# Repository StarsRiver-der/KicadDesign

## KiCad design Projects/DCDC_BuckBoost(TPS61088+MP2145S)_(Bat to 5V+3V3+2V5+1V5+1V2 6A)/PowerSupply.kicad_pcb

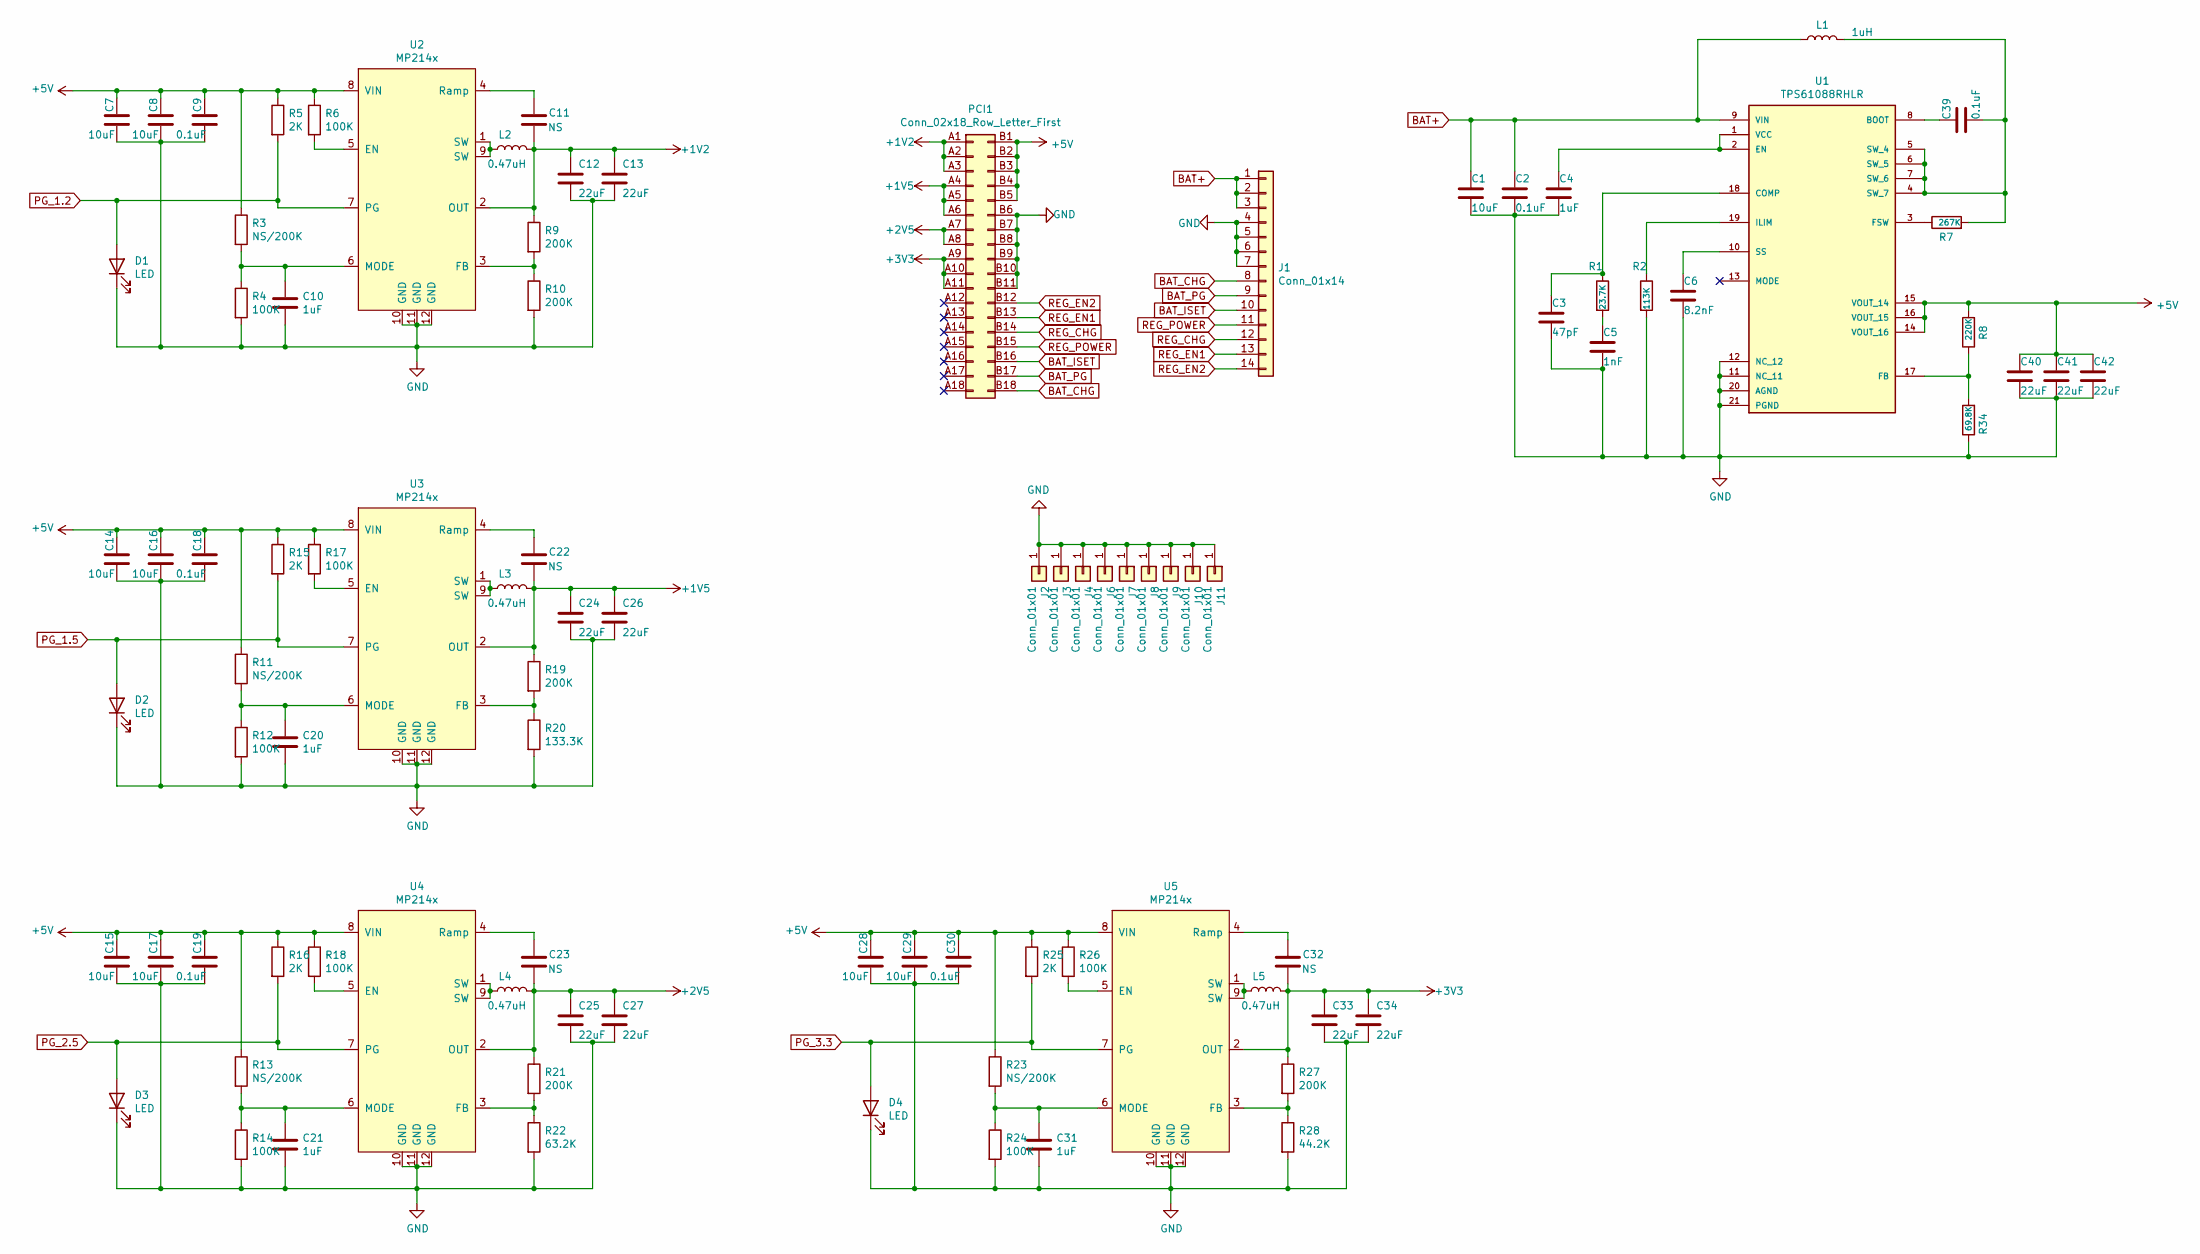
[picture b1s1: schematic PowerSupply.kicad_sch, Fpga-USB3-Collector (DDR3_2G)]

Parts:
C1, C7, C8, C14, C15, C16, C17, C28, C29: 10uF; C_0603_1608Metric
C2, C9, C18, C19, C30, C39: 0.1uF; C_0402_1005Metric
C3: 47pF; C_0402_1005Metric
C4, C10, C20, C21, C31: 1uF; C_0402_1005Metric
C5: 1nF; C_0402_1005Metric
C6: 8.2nF; C_0402_1005Metric
C11, C22, C23, C32: NS; C_0402_1005Metric
C12, C13, C24, C25, C26, C27, C33, C34, C40, C41, C42: 22uF; C_0603_1608Metric
D1, D2, D3, D4: LED; LED_0402_1005Metric
J1: Conn_01x14; Hirose_FH12-14S-0.5SH_1x14-1MP_P0.50mm_Horizontal
J2, J3, J4, J6, J7, J8, J9, J10, J11: Conn_01x01; pad-6-1.5
L1: 1uH; L_Sunlord_MWSA0518_5.4x5.2mm
L2, L3, L4, L5: 0.47uH; L_Sunlord_MWSA0518_5.4x5.2mm
PCI1: Conn_02x18_Row_Letter_First; BUS_PCIexpress_x1
R1: 23.7K; R_0402_1005Metric
R2: 113K; R_0402_1005Metric
R3, R11, R13, R23: NS/200K; R_0402_1005Metric
R4, R6, R12, R14, R17, R18, R24, R26: 100K; R_0402_1005Metric
R5, R15, R16, R25: 2K; R_0402_1005Metric
R7: 267K; R_0402_1005Metric
R8: 220K; R_0402_1005Metric
R9, R10, R19, R21, R27: 200K; R_0402_1005Metric
R20: 133.3K; R_0402_1005Metric
R22: 63.2K; R_0402_1005Metric
R28: 44.2K; R_0402_1005Metric
R34: 69.8K; R_0402_1005Metric
U1: TPS61088RHLR; IC_TPS61088RHLR; PARTREV 4219071/A 05/2017
U2, U3, U4, U5: MP214x; MP2145_2147_DG_Z

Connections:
+1V2: C11.1, C12.1, C13.1, L2.2, PCI1.A1, PCI1.A2, PCI1.A3, R9.1, U2.2 (OUT)
+1V5: C22.1, C24.1, C26.1, L3.2, PCI1.A4, PCI1.A5, PCI1.A6, R19.1, U3.2 (OUT)
+2V5: C23.1, C25.1, C27.1, L4.2, PCI1.A7, PCI1.A8, R21.1, U4.2 (OUT)
+3V3: C32.1, C33.1, C34.1, L5.2, PCI1.A9, PCI1.A10, PCI1.A11, R27.1, U5.2 (OUT)
+5V: C7.1, C8.1, C9.1, C14.1, C15.1, C16.1, C17.1, C18.1, C19.1, C28.1, C29.1, C30.1, C40.1, C41.1, C42.1, PCI1.B1, PCI1.B2, PCI1.B3, PCI1.B4, PCI1.B5, R3.1, R5.1, R6.1, R8.2, R11.1, R13.1, R15.1, R16.1, R17.1, R18.1, R23.1, R25.1, R26.1, U1.14 (VOUT_16), U1.15 (VOUT_14), U1.16 (VOUT_15), U2.8 (VIN), U3.8 (VIN), U4.8 (VIN), U5.8 (VIN)
BAT+: C1.1, C2.1, J1.1, J1.2, J1.3, L1.1, U1.9 (VIN)
BAT_CHG: J1.8, PCI1.B18
BAT_ISET: J1.10, PCI1.B16
BAT_PG: J1.9, PCI1.B17
GND: C1.2, C2.2, C3.2, C4.2, C5.2, C6.2, C7.2, C8.2, C9.2, C10.2, C12.2, C13.2, C14.2, C15.2, C16.2, C17.2, C18.2, C19.2, C20.2, C21.2, C24.2, C25.2, C26.2, C27.2, C28.2, C29.2, C30.2, C31.2, C33.2, C34.2, C40.2, C41.2, C42.2, D1.1 (K), D2.1 (K), D3.1 (K), D4.1 (K), J1.4, J1.5, J1.6, J1.7, J2.1, J3.1, J4.1, J6.1, J7.1, J8.1, J9.1, J10.1, J11.1, PCI1.B6, PCI1.B7, PCI1.B8, PCI1.B9, PCI1.B10, PCI1.B11, R2.2, R4.2, R10.2, R12.2, R14.2, R20.2, R22.2, R24.2, R28.2, R34.1, U1.11 (NC_11), U1.12 (NC_12), U1.20 (AGND), U1.21 (PGND), U2.10 (GND), U2.11 (GND), U2.12 (GND), U3.10 (GND), U3.11 (GND), U3.12 (GND), U4.10 (GND), U4.11 (GND), U4.12 (GND), U5.10 (GND), U5.11 (GND), U5.12 (GND)
unnamed: C3.1, R1.1, U1.18 (COMP)
unnamed: C4.1, U1.1 (VCC), U1.2 (EN)
unnamed: C5.1, R1.2
unnamed: C6.1, U1.10 (SS)
unnamed: C10.1, R3.2, R4.1, U2.6 (MODE)
unnamed: C11.2, U2.4 (Ramp)
unnamed: C20.1, R11.2, R12.1, U3.6 (MODE)
unnamed: C21.1, R13.2, R14.1, U4.6 (MODE)
unnamed: C22.2, U3.4 (Ramp)
unnamed: C23.2, U4.4 (Ramp)
unnamed: C31.1, R23.2, R24.1, U5.6 (MODE)
unnamed: C32.2, U5.4 (Ramp)
unnamed: C39.1, U1.8 (BOOT)
unnamed: C39.2, L1.2, R7.2, U1.4 (SW_7), U1.5 (SW_4), U1.6 (SW_5), U1.7 (SW_6)
unnamed: L2.1, U2.1 (SW), U2.9 (SW)
unnamed: L3.1, U3.1 (SW), U3.9 (SW)
unnamed: L4.1, U4.1 (SW), U4.9 (SW)
unnamed: L5.1, U5.1 (SW), U5.9 (SW)
unnamed: R2.1, U1.19 (ILIM)
unnamed: R6.2, U2.5 (EN)
unnamed: R7.1, U1.3 (FSW)
unnamed: R9.2, R10.1, U2.3 (FB)
unnamed: R17.2, U3.5 (EN)
unnamed: R18.2, U4.5 (EN)
unnamed: R19.2, R20.1, U3.3 (FB)
unnamed: R21.2, R22.1, U4.3 (FB)
unnamed: R26.2, U5.5 (EN)
unnamed: R27.2, R28.1, U5.3 (FB)
unnamed: R8.1, R34.2, U1.17 (FB)
PG_1.2: D1.2 (A), R5.2, U2.7 (PG)
PG_1.5: D2.2 (A), R15.2, U3.7 (PG)
PG_2.5: D3.2 (A), R16.2, U4.7 (PG)
PG_3.3: D4.2 (A), R25.2, U5.7 (PG)
REG_CHG: J1.12, PCI1.B14
REG_EN1: J1.13, PCI1.B13
REG_EN2: J1.14, PCI1.B12
REG_POWER: J1.11, PCI1.B15

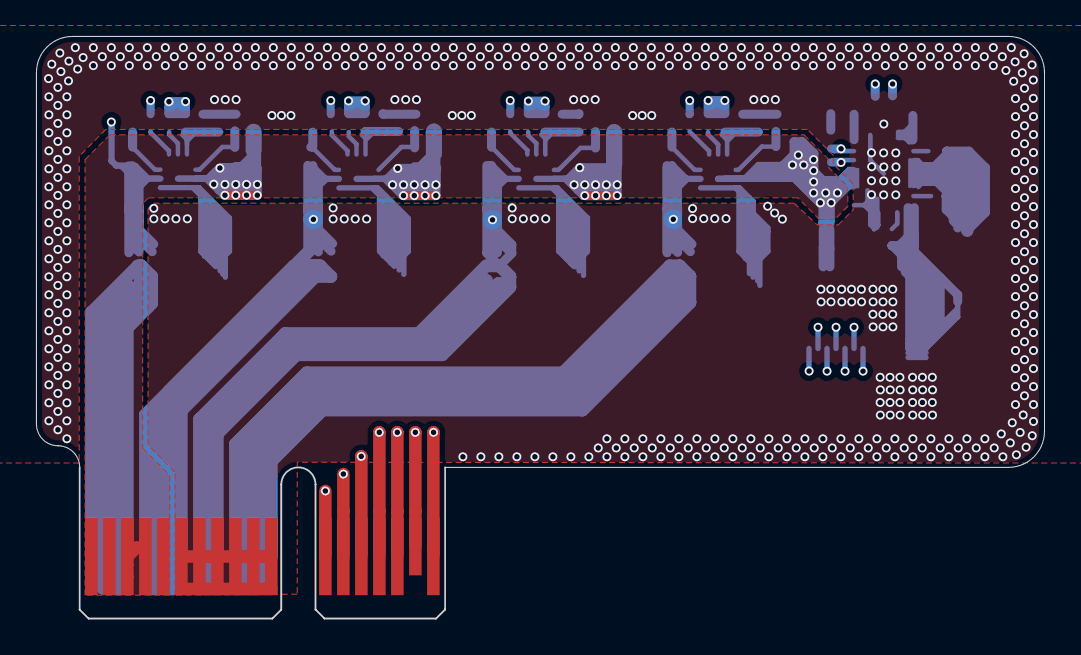
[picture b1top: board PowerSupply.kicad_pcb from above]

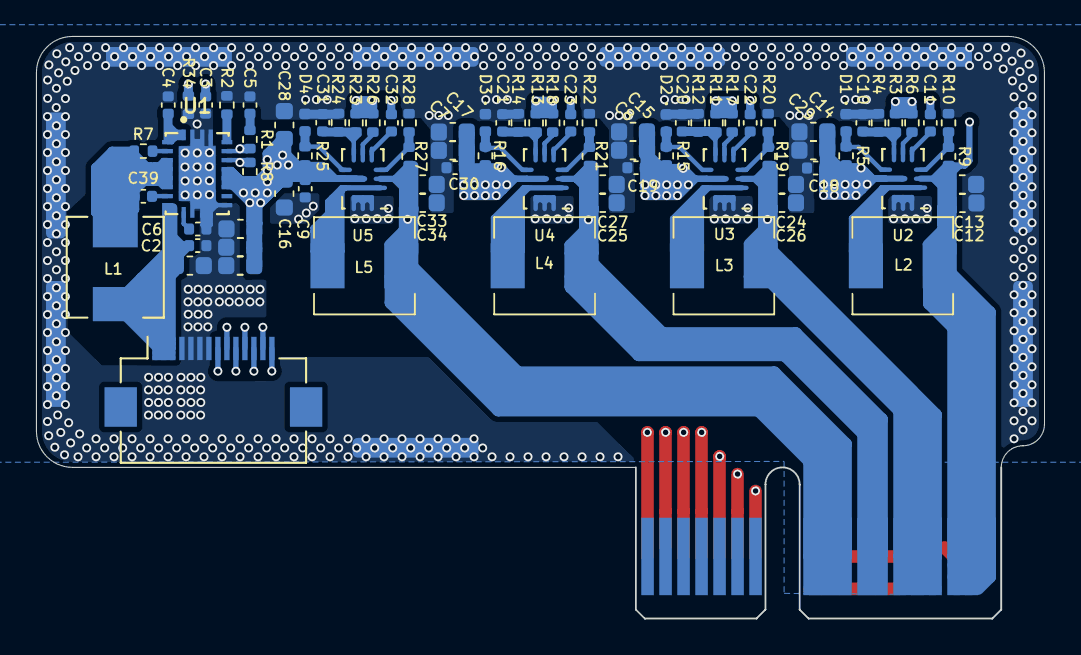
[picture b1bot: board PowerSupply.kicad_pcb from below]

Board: 4 copper layers, 56.0 x 32.3 mm, 92 parts (91 on the bottom side), 47 nets.

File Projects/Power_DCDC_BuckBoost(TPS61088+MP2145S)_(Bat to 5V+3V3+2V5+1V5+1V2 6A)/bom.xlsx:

标号 | 数量/板 | 值 | 备注 | 封装 | 数量 | 单价 | 总价
C1, C7, C8, C14, C15, C16, C17, C28, C29 | 9 | 10uF |  | 0603 | 100 | 0 | 0
C2, C9, C18, C19, C30, C39 | 6 | 0.1uF |  | 0402 | 100 | 0 | 0
C3 | 1 | 47pF |  | 0402 | 100 | 0 | 0
C4, C10, C20, C21, C31 | 5 | 1uF |  | 0402 | 100 | 0 | 0
C5 | 1 | 1nF |  | 0402 | 100 | 0 | 0
C6 | 1 | 8.2nF |  | 0402 | 100 | 0 | 0
C11, C22, C23, C32 | 4 | NS |  | 0402 | 100 | 0 | 0
C12, C13, C24, C25, C26, C27, C33, C34, C40, C41, C42 | 11 | 22uF |  | 0603 | 100 | 0 | 0
D1, D2, D3, D4 | 4 | LED |  | 0402 | 100 | 0 | 0
J1 | 1 | Conn_01x14 |  | FPC:14S-0.5SH | 100 | 0 | 0
L1 | 1 | 1uH |  | 0530 | 100 | 0 | 0
L2, L3, L4, L5 | 4 | 0.47uH |  | 0530 | 100 | 0 | 0
R1 | 1 | 23.7K |  | 0402 | 100 | 0 | 0
R2 | 1 | 113K |  | 0402 | 100 | 0 | 0
R3, R11, R13, R23 | 4 | NS/200K |  | 0402 | 100 | 0 | 0
R4, R6, R12, R14, R17, R18, R24, R26 | 8 | 100K |  | 0402 | 100 | 0 | 0
R5, R15, R16, R25 | 4 | 2K |  | 0402 | 100 | 0 | 0
R7 | 1 | 267K |  | 0402 | 100 | 0 | 0
R8 | 1 | 220K |  | 0402 | 100 | 0 | 0
R9, R10, R19, R21, R27 | 5 | 200K |  | 0402 | 100 | 0 | 0
R20 | 1 | 133.3K |  | 0402 | 100 | 0 | 0
R22 | 1 | 63.2K |  | 0402 | 100 | 0 | 0
R28 | 1 | 44.2K |  | 0402 | 100 | 0 | 0
R34 | 1 | 69.8K |  | 0402 | 100 | 0 | 0
U1 | 1 | TPS61088RHLR |  | TPS61088RHLR | 100 | 0 | 0
U2, U3, U4, U5 | 4 | MP2145 |  | MP2145 | 100 | 0 | 0

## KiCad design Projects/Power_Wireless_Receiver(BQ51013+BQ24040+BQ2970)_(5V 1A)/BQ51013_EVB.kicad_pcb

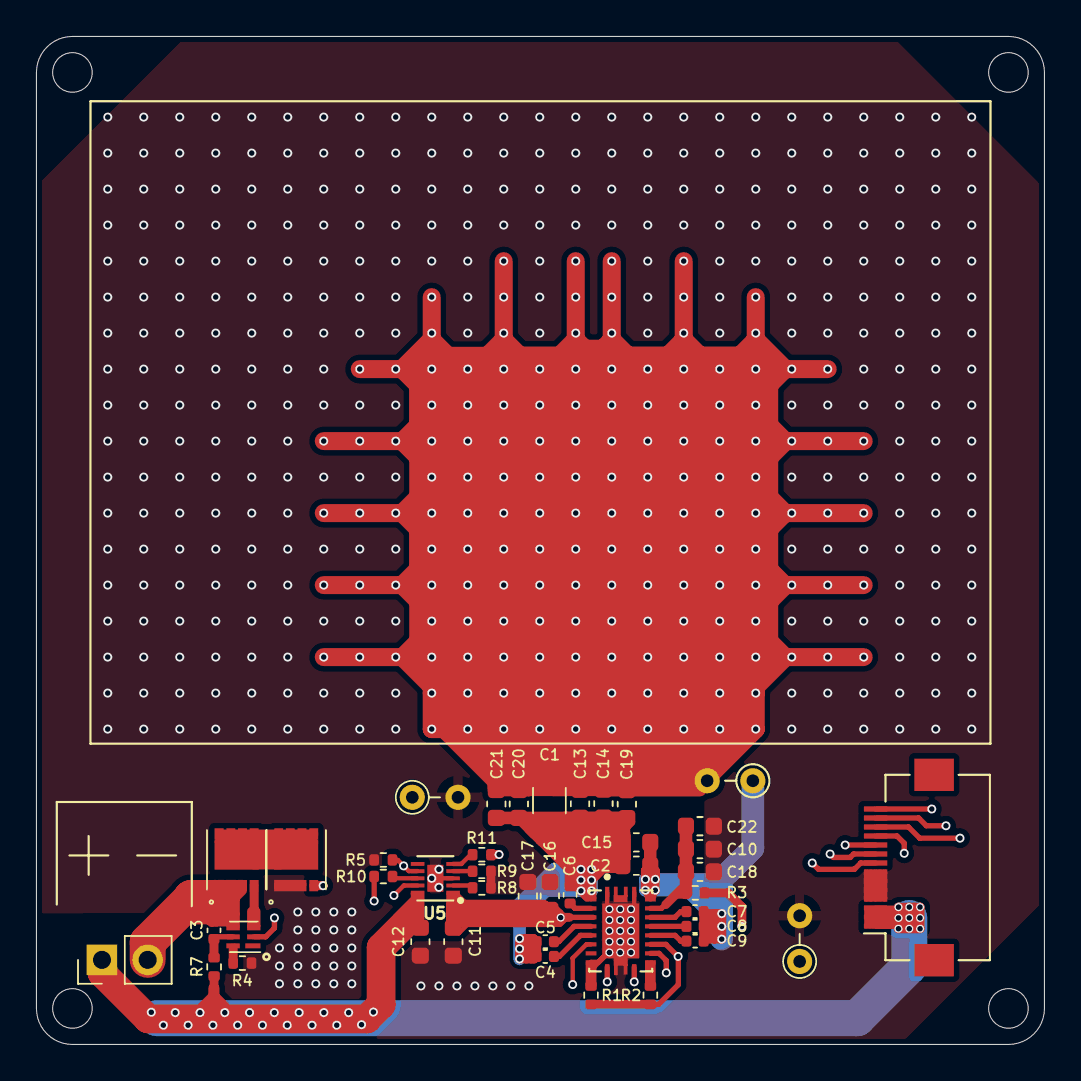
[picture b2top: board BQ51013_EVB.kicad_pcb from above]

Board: 4 copper layers, 56.0 x 56.0 mm, 46 parts (0 on the bottom side), 33 nets.

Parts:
C1: 100nF; C_1206_3216Metric
C2, C15: 1nF; C_0603_1608Metric
C3: 100nF; C_0402_1005Metric
C4, C9: 22nF; C_0402_1005Metric
C5, C8: 470nF; C_0402_1005Metric
C6, C7: 10nF; C_0402_1005Metric
C10, C16, C22: 10uF; C_0603_1608Metric
C11, C12: 1uF; C_0603_1608Metric
C13, C14, C19, C20: 10nF; C_0603_1608Metric
C17, C18: 0.1uF; C_0603_1608Metric
C21: 2.2nF; C_0603_1608Metric
J1, J2, J3, J4: Conn_01x01_Female; MountingHole_2.2mm_M2
J5: BAT; PinHeader_1x02_P2.54mm_Vertical
J6: AC; R_Axial_DIN0204_L3.6mm_D1.6mm_P2.54mm_Vertical
J7: Conn_01x14; Hirose_FH12-14S-0.5SH_1x14-1MP_P0.50mm_Horizontal
R1: 196R; R_0402_1005Metric
R2: 20R; R_0402_1005Metric
R3: 20k; R_0402_1005Metric
R4: 2.2k; R_0402_1005Metric
R5: 1k; R_0402_1005Metric
R7: 330R; R_0402_1005Metric
R8: 536R; R_0402_1005Metric
R9: 2K; R_0402_1005Metric
R10, R11: 1.5K; R_0402_1005Metric
TH1, TH2: Thermistor_NTC; R_Axial_DIN0204_L3.6mm_D1.6mm_P2.54mm_Vertical
U1: BQ2971; WSON-6_1.5x1.5mm_P0.5mm
U2: BQ51013BRHLR
U3, U4: CSD16406Q3
U5: BQ24040DSQT

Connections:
BAT+: C12.1, J5.1, J7.1, J7.2, J7.3, R7.1, U5.10 (OUT)
BAT-: C3.2, J5.2, U1.4 (VSS), U4.1, U4.2, U4.3
BAT_CHG: J7.8, R10.2
BAT_ISET: J7.10, R5.1, U5.7 (ISET2)
BAT_PG: J7.9, R11.2
GND: C10.1, C11.1, C12.2, C16.1, C17.1, C18.1, C22.1, J7.4, J7.5, J7.6, J7.7, R1.2, R4.2, R5.2, R8.2, R9.2, TH1.2, TH2.2, U2.1 (PGND), U2.9 (AD), U2.20 (PGND), U2.21 (EXP), U3.1, U3.2, U3.3, U5.3 (VSS), U5.11 (EP)
unnamed: C1.1, C13.1, C14.1, C19.1, C20.1, C21.1, J6.2
unnamed: C1.2, C2.1, C4.1, C5.1, C6.1, C13.2, C14.2, C15.1, C19.2, C20.2, C21.2, U2.2 (AC1)
unnamed: C3.1, R7.2, U1.5 (BAT)
unnamed: C4.2, U2.6 (COMM1)
unnamed: C5.2, U2.5 (CLAMP1)
unnamed: C6.2, U2.3 (BOOT1)
unnamed: C7.1, U2.17 (BOOT2)
unnamed: C8.1, U2.16 (CLAMP2)
unnamed: C9.1, U2.15 (COMM2)
unnamed: C10.2, C18.2, C22.2, R3.1, U2.18 (RECT)
unnamed: C2.2, C7.2, C8.2, C9.2, C15.2, J6.1, U2.19 (AC2)
unnamed: R1.1, R2.2, R3.2, U2.14 (FOD)
unnamed: R2.1, U2.12 (ILIM)
unnamed: R4.1, U1.6 (V-)
unnamed: R8.1, U5.2 (ISET)
unnamed: R9.1, U5.4 (PRETERM)
unnamed: R10.1, U5.8 (~CHG)
unnamed: R11.1, U5.5 (~PG)
unnamed: TH1.1, U2.13 (TS/CTRL)
unnamed: TH2.1, U5.9 (TS)
unnamed: U1.2 (COUT), U3.4
unnamed: U1.3 (DOUT), U4.4
unnamed: U3.5, U3.6, U3.7, U3.8, U4.5, U4.6, U4.7, U4.8
REG_CHG: J7.12, U2.7 (~CHG)
REG_EN1: J7.13, U2.10 (EN1)
REG_EN2: J7.14, U2.11 (EN2)
REG_power: C11.2, C16.2, C17.2, J7.11, U2.4 (OUT), U5.1 (IN)

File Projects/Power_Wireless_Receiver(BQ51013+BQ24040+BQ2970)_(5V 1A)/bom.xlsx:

标号 | 数量/板 | 值 | 类型 | 封装 | 数量 | 单价 | 总价
C1 | 1 | 100nF |  | 1206 | 100 | 0 | 0
C2, C15 | 2 | 1nF |  | 0603 | 100 | 0 | 0
C3 | 1 | 100nF |  | 0402 | 100 | 0 | 0
C4, C9 | 2 | 22nF |  | 0402 | 100 | 0 | 0
C5, C8 | 2 | 470nF |  | 0402 | 100 | 0 | 0
C6, C7 | 2 | 10nF |  | 0402 | 100 | 0 | 0
C10, C16, C22 | 3 | 10uF |  | 0603 | 100 | 0 | 0
C11, C12 | 2 | 1uF |  | 0603 | 100 | 0 | 0
C13, C14, C19, C20 | 4 | 10nF |  | 0603 | 100 | 0 | 0
C17, C18 | 2 | 0.1uF |  | 0603 | 100 | 0 | 0
C21 | 1 | 2.2nF |  | 0603 | 100 | 0 | 0
J5 | 1 | BAT |  | 2.54mm:PinHeader | 100 | 0 | 0
J7 | 1 | Conn_01x14 |  | FPC:14S-0.5SH | 100 | 0 | 0
R1 | 1 | 196R |  | 0402 | 100 | 0 | 0
R2 | 1 | 20R |  | 0402 | 100 | 0 | 0
R3 | 1 | 20k |  | 0402 | 100 | 0 | 0
R4 | 1 | 2.2k |  | 0402 | 100 | 0 | 0
R5 | 1 | 1k |  | 0402 | 100 | 0 | 0
R7 | 1 | 330R |  | 0402 | 100 | 0 | 0
R8 | 1 | 536R |  | 0402 | 100 | 0 | 0
R9 | 1 | 2K |  | 0402 | 100 | 0 | 0
R10, R11 | 2 | 1.5K |  | 0402 | 100 | 0 | 0
TH1, TH2 | 2 | 103AT-2 |  |  | 100 | 0 | 0
U1 | 1 | BQ2971 |  | WSON-6_1.5x1.5mm_P0.5mm | 100 | 0 | 0
U2 | 1 | BQ51013BRHLR |  | BQ51013BRHLR | 100 | 0 | 0
U3, U4 | 2 | CSD16406Q3 |  | CSD16406Q3 | 100 | 0 | 0
U5 | 1 | BQ24040DSQT |  | BQ24040DSQT | 100 | 0 | 0

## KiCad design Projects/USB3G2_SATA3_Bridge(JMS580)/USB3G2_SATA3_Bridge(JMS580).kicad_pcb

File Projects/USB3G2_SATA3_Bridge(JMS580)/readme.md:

# 硬盘转接卡
SATA6 转 Type-C，USB3.1 Gen2

# 高速差分线注意
* 四层板，阻抗控制使用`2313压层`结构

# 预览
/preview.jpg)

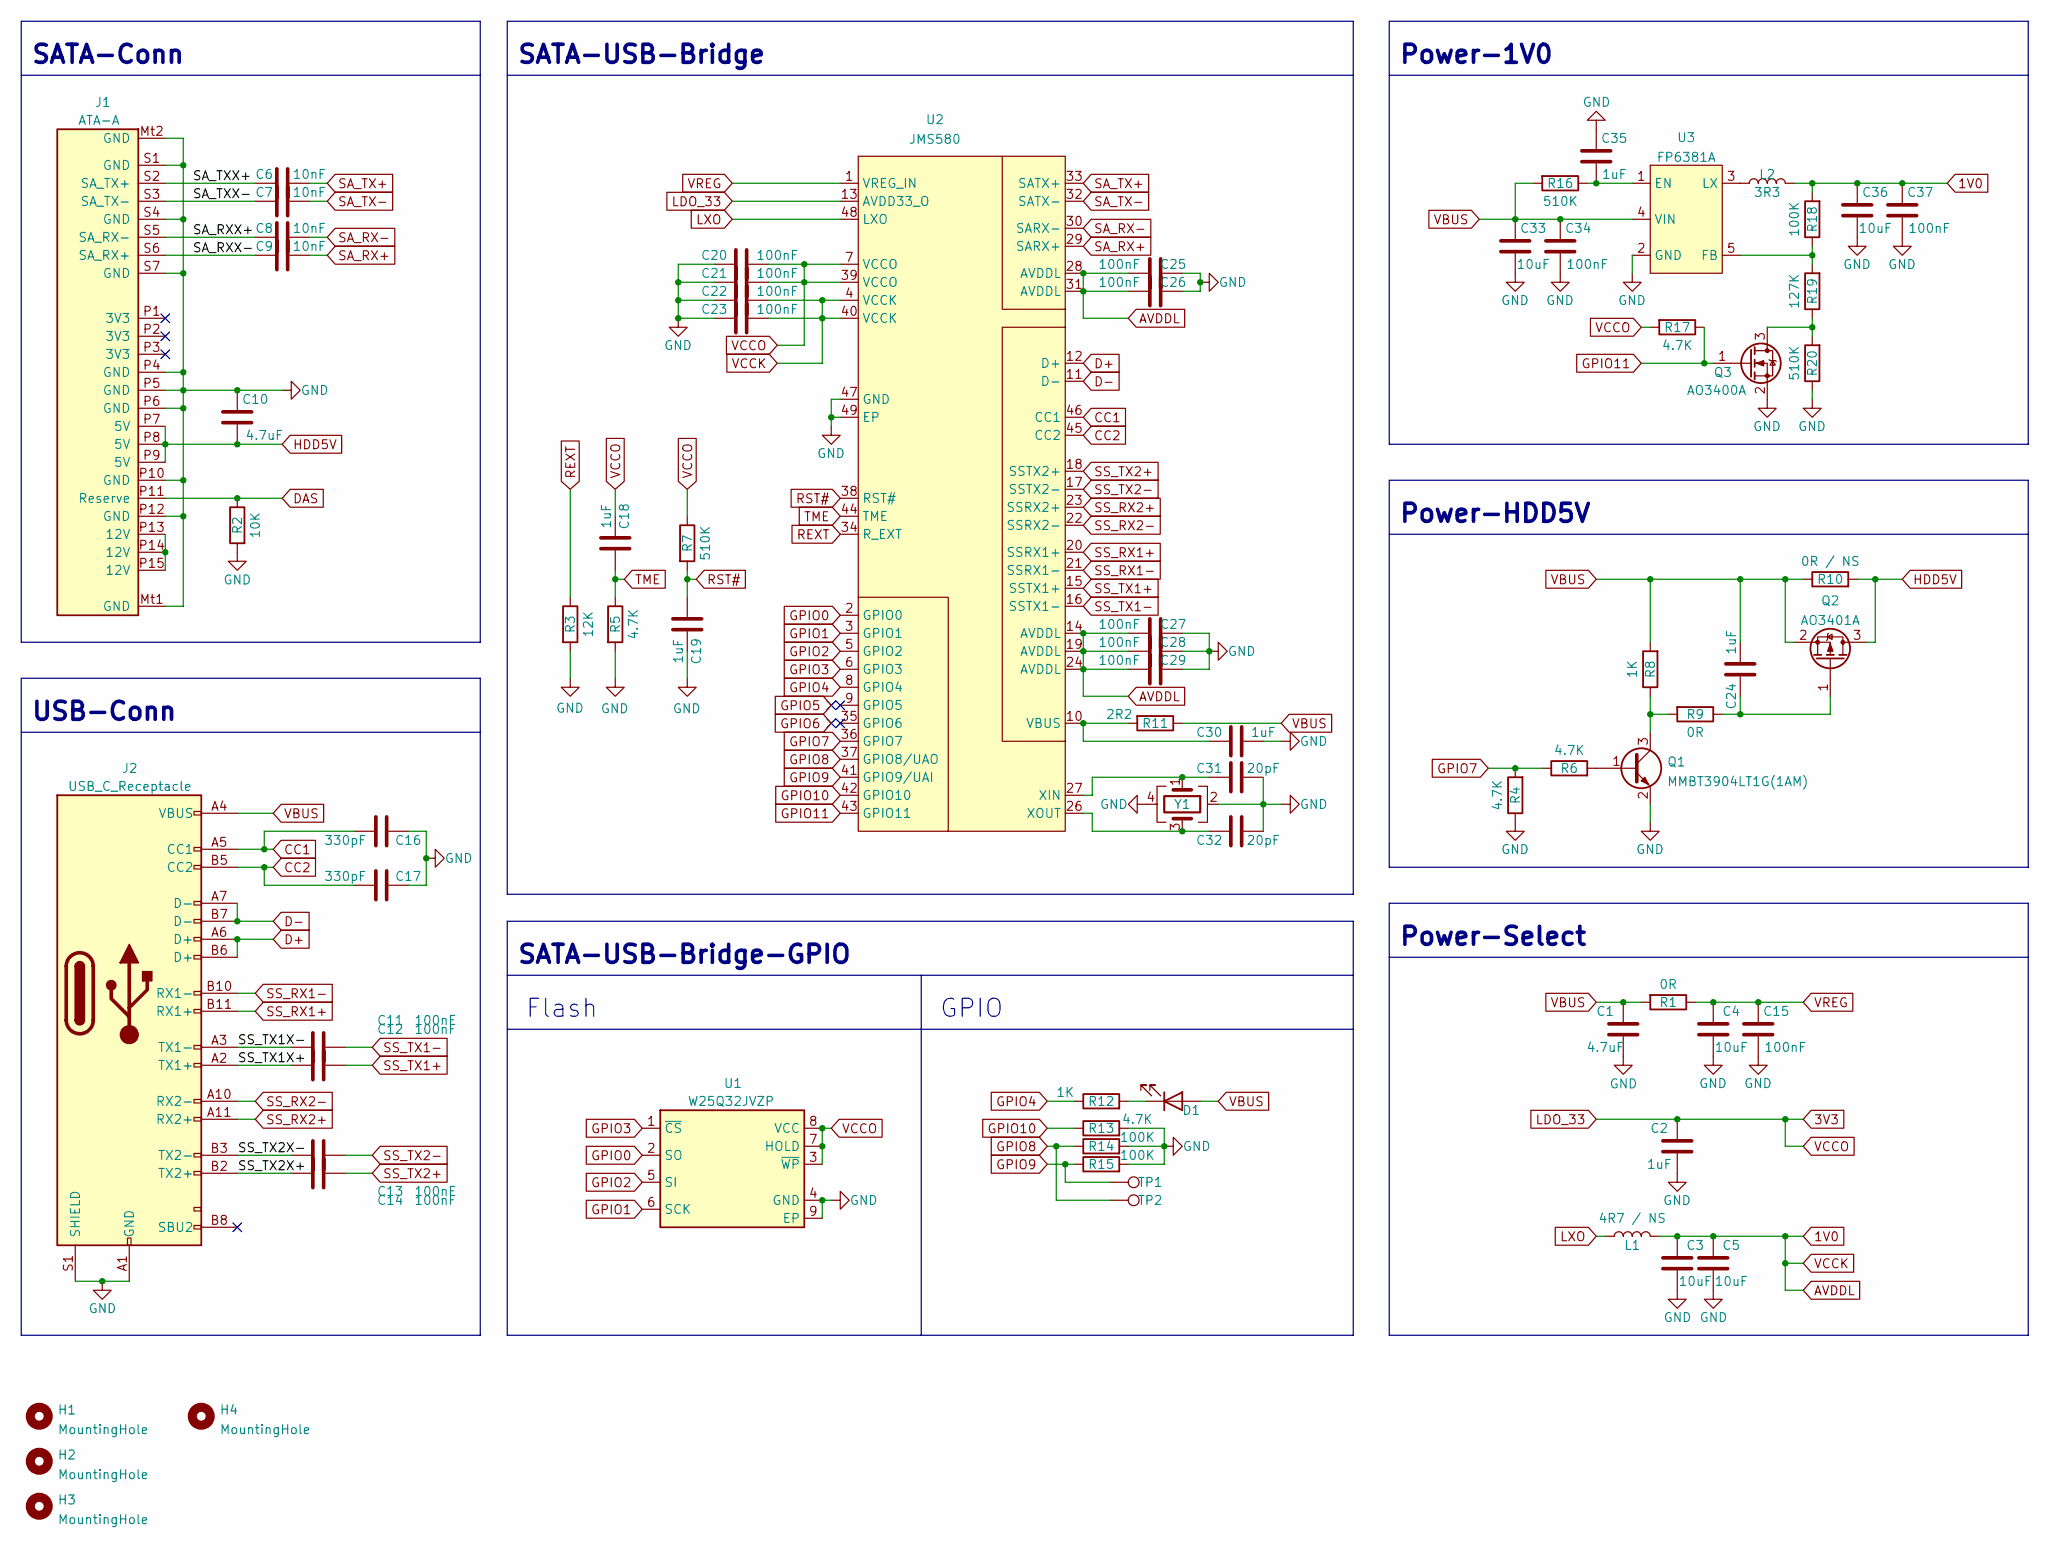
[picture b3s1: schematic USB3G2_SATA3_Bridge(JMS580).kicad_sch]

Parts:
C1, C10: 4.7uF; C_0402_1005Metric
C2, C18, C19, C24, C30, C35: 1uF; C_0402_1005Metric
C3, C4, C5, C33, C36: 10uF; C_0402_1005Metric
C6, C7, C8, C9: 10nF; C_0402_1005Metric
C11, C12, C13, C14, C15, C20, C21, C22, C23, C25, C26, C27, C28, C29, C34, C37: 100nF; C_0402_1005Metric
C16, C17: 330pF; C_0402_1005Metric
C31, C32: 20pF; C_0402_1005Metric
D1: LED; LED_0402_1005Metric
H1, H2, H3: MountingHole; MountingHole_2.2mm_M2_Pad_Via
H4: MountingHole; ESD-Logo_6.6x6mm_SilkScreen
J1: ATA-A; SATA-22P-M
J2: USB_C_Receptacle; USB-C_24p
L1: 4R7 / NS; L_Neosid_SMS-ME3015
L2: 3R3; L_Neosid_SMS-ME3015
Q1: MMBT3904LT1G(1AM); SOT-23
Q2: AO3401A; SOT-23
Q3: AO3400A; SOT-23
R1: 0R; R_0603_1608Metric
R2: 10K; R_0402_1005Metric
R3: 12K; R_0402_1005Metric
R4, R5, R6, R13, R17: 4.7K; R_0402_1005Metric
R7, R16, R20: 510K; R_0402_1005Metric
R8, R12: 1K; R_0402_1005Metric
R9: 0R; R_0402_1005Metric
R10: 0R / NS; R_0402_1005Metric
R11: 2R2; R_0402_1005Metric
R14, R15, R18: 100K; R_0402_1005Metric
R19: 127K; R_0402_1005Metric
TP1, TP2: TestPoint; TestPoint_Pad_D1.0mm
U1: W25Q32JVZP; WSON-8-1EP_6x5mm_P1.27mm_EP3.4x4.3mm
U2: JMS580; QFN-48-1EP_6x6mm_P0.4mm_EP4.3x4.3mm
U3: FP6381A; SOT-23-5
Y1: Crystal_GND24; Oscillator_SMD_ECS_2520MV-xxx-xx-4Pin_2.5x2.0mm

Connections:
1V0: C3.1, C5.1, C22.1, C23.1, C25.1, C26.1, C27.1, C28.1, C29.1, C36.2, C37.2, L1.1, L2.1, R18.2, U2.4 (VCCK), U2.14 (AVDDL), U2.19 (AVDDL), U2.24 (AVDDL), U2.28 (AVDDL), U2.31 (AVDDL), U2.40 (VCCK)
/SA_RXX+: C8.2, J1.S5 (SA_RX-)
/SA_RXX-: C9.2, J1.S6 (SA_RX+)
/SA_TXX+: C6.2, J1.S2 (SA_TX+)
/SA_TXX-: C7.2, J1.S3 (SA_TX-)
/SS_TX1X+: C12.2, J2.A2 (TX1+)
/SS_TX1X-: C11.2, J2.A3 (TX1-)
/SS_TX2X+: C14.2, J2.B2 (TX2+)
/SS_TX2X-: C13.2, J2.B3 (TX2-)
CC1: C16.2, J2.A5 (CC1), U2.46 (CC1)
CC2: C17.2, J2.B5 (CC2), U2.45 (CC2)
D+: J2.A6 (D+), J2.B6 (D+), U2.12 (D+)
D-: J2.A7 (D-), J2.B7 (D-), U2.11 (D-)
DAS: J1.P11 (Reserve), R2.1
GND: C1.1, C2.2, C3.2, C4.1, C5.2, C10.2, C15.1, C16.1, C17.1, C19.1, C20.2, C21.2, C22.2, C23.2, C25.2, C26.2, C27.2, C28.2, C29.2, C30.1, C31.2, C32.2, C33.1, C34.1, C35.2, C36.1, C37.1, J1.Mt1 (GND), J1.Mt2 (GND), J1.P4 (GND), J1.P5 (GND), J1.P6 (GND), J1.P10 (GND), J1.P12 (GND), J1.S1 (GND), J1.S4 (GND), J1.S7 (GND), J2.A1 (GND), J2.A12 (GND), J2.B1 (GND), J2.B12 (GND), J2.S1 (SHIELD), Q1.2 (E), Q3.2 (S), R2.2, R3.2, R4.1, R5.2, R13.2, R14.2, R15.2, R20.1, U1.4 (GND), U1.9 (EP), U2.47 (GND), U2.49 (EP), U3.2 (GND), Y1.2, Y1.4
GPIO0: U1.2 (SO), U2.2 (GPIO0)
GPIO1: U1.6 (SCK), U2.3 (GPIO1)
GPIO2: U1.5 (SI), U2.5 (GPIO2)
GPIO3: U1.1 (~CS), U2.6 (GPIO3)
GPIO4: R12.1, U2.8 (GPIO4)
GPIO7: R4.2, R6.1, U2.36 (GPIO7)
GPIO8: R14.1, TP2.1, U2.37 (GPIO8/UAO)
GPIO9: R15.1, TP1.1, U2.41 (GPIO9/UAI)
GPIO10: R13.1, U2.42 (GPIO10)
GPIO11: Q3.1 (G), R17.1, U2.43 (GPIO11)
HDD5V: C10.1, J1.P7 (5V), J1.P8 (5V), J1.P9 (5V), Q2.3 (D), R10.2
LDO_33: C2.1, C18.2, C20.1, C21.1, R7.1, R17.2, U1.3 (~WP), U1.7 (HOLD), U1.8 (VCC), U2.7 (VCCO), U2.13 (AVDD33_O), U2.39 (VCCO)
LXO: L1.2, U2.48 (LXO)
unnamed: C24.2, Q2.1 (G), R9.1
unnamed: C30.2, R11.2, U2.10 (VBUS)
unnamed: C31.1, U2.27 (XIN), Y1.1
unnamed: C32.1, U2.26 (XOUT), Y1.3
unnamed: C35.1, R16.1, U3.1 (EN)
unnamed: D1.1 (K), R12.2
unnamed: J1.P13 (12V), J1.P14 (12V), J1.P15 (12V)
unnamed: L2.2, U3.3 (LX)
unnamed: Q1.1 (B), R6.2
unnamed: Q1.3 (C), R8.1, R9.2
unnamed: Q3.3 (D), R19.1, R20.2
unnamed: R18.1, R19.2, U3.5 (FB)
REXT: R3.1, U2.34 (R_EXT)
RST#: C19.2, R7.2, U2.38 (RST#)
SA_RX+: C9.1, U2.29 (SARX+)
SA_RX-: C8.1, U2.30 (SARX-)
SA_TX+: C6.1, U2.33 (SATX+)
SA_TX-: C7.1, U2.32 (SATX-)
SS_RX1+: J2.B11 (RX1+), U2.20 (SSRX1+)
SS_RX1-: J2.B10 (RX1-), U2.21 (SSRX1-)
SS_RX2+: J2.A11 (RX2+), U2.23 (SSRX2+)
SS_RX2-: J2.A10 (RX2-), U2.22 (SSRX2-)
SS_TX1+: C12.1, U2.15 (SSTX1+)
SS_TX1-: C11.1, U2.16 (SSTX1-)
SS_TX2+: C14.1, U2.18 (SSTX2+)
SS_TX2-: C13.1, U2.17 (SSTX2-)
TME: C18.1, R5.1, U2.44 (TME)
VBUS: C1.2, C24.1, C33.2, C34.2, D1.2 (A), J2.A4 (VBUS), J2.A9 (VBUS), J2.B4 (VBUS), J2.B9 (VBUS), Q2.2 (S), R1.2, R8.2, R10.1, R11.1, R16.2, U3.4 (VIN)
VREG: C4.2, C15.2, R1.1, U2.1 (VREG_IN)

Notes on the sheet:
Power-Select
Flash
SATA-USB-Bridge-GPIO
Power-HDD5V
SATA-Conn
USB-Conn
SATA-USB-Bridge
Power-1V0
GPIO

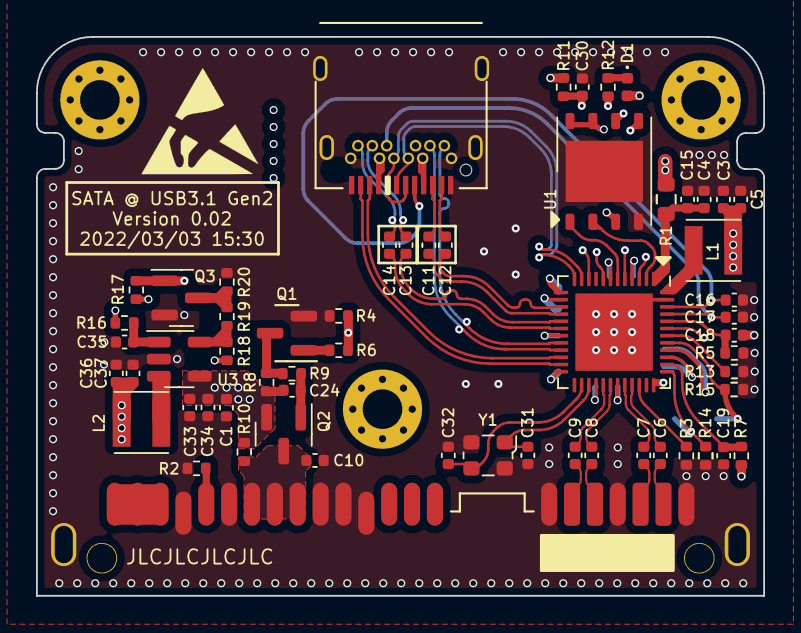
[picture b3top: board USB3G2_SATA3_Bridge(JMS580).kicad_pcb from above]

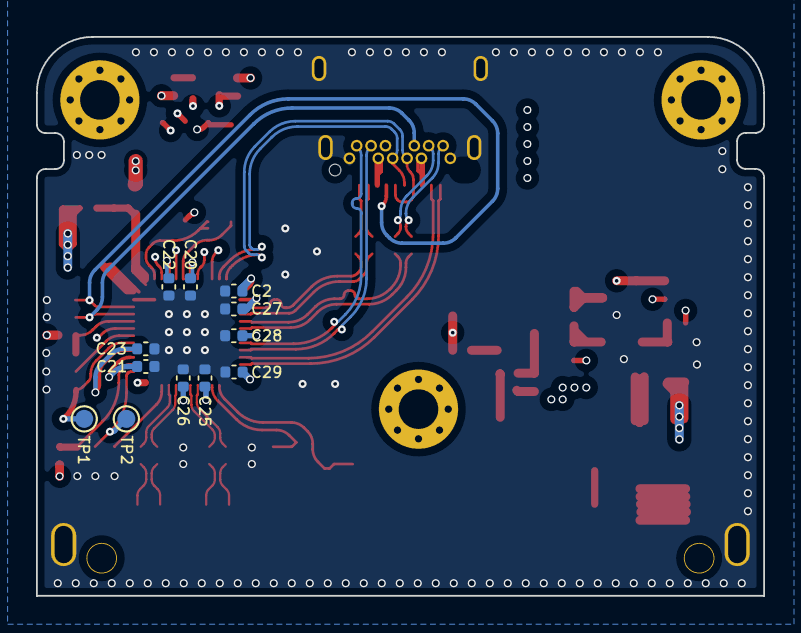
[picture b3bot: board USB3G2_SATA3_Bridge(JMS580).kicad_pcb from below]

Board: 4 copper layers, 40.4 x 31.1 mm, 75 parts (12 on the bottom side), 57 nets.

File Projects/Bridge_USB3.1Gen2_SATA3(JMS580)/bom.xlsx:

元件 | 数量/板 | 值 | 备注 | 封装 | 数量 | 单价 | 总价
C1, C10 | 2 | 4.7uF |  | 0402 | 100 | 0 | 0
C2, C18, C19, C24, C30, C35 | 6 | 1uF |  | 0402 | 100 | 0 | 0
C3, C4, C5, C33, C36 | 5 | 10uF |  | 0402 | 100 | 0 | 0
C6, C7, C8, C9 | 4 | 10nF |  | 0402 | 100 | 0 | 0
C11, C12, C13, C14, C15, C20, C21, C22, C23, C25, C26, C27, C28, C29, C34, C37 | 16 | 100nF |  | 0402 | 100 | 0 | 0
C16, C17 | 2 | 330pF |  | 0402 | 100 | 0 | 0
C31, C32 | 2 | 20pF |  | 0402 | 100 | 0 | 0
D1 | 1 | LED |  | 0402 | 100 | 0 | 0
J1 | 1 | ATA-A |  | SATA-22P-M | 10 | 0 | 0
J2 | 1 | USB_C_Receptacle |  | USB-C_24p | 10 | 0 | 0
L1 | 1 | 4R7 / NS |  | NR3015 | 50 | 0 | 0
L2 | 1 | 3R3 |  | NR3015 | 50 | 0 | 0
Q1 | 1 | MMBT3904LT1G(1AM) |  | SOT-23 | 100 | 0 | 0
Q2 | 1 | AO3401A |  | SOT-23 | 100 | 0 | 0
Q3 | 1 | AO3400A |  | SOT-23 | 100 | 0 | 0
R1 | 1 | 0R |  | 0603 | 100 | 0 | 0
R2 | 1 | 10K |  | 0402 | 100 | 0 | 0
R3 | 1 | 12K |  | 0402 | 100 | 0 | 0
R4, R5, R6, R13, R17 | 5 | 4.7K |  | 0402 | 100 | 0 | 0
R7, R16, R20 | 3 | 510K |  | 0402 | 100 | 0 | 0
R8, R12 | 2 | 1K |  | 0402 | 100 | 0 | 0
R9 | 1 | 0R |  | 0402 | 100 | 0 | 0
R10 | 1 | 0R / NS |  | 0402 | 100 | 0 | 0
R11 | 1 | 2R2 |  | 0402 | 100 | 0 | 0
R14, R15, R18 | 3 | 100K |  | 0402 | 100 | 0 | 0
R19 | 1 | 127K |  | 0402 | 100 | 0 | 0
U1 | 1 | W25Q32JVZP |  | WSON-8-1EP | 5 | 0 | 0
U2 | 1 | JMS580 |  | QFN-48-1EP | 5 | 0 | 0
U3 | 1 | FP6381A |  | SOT-23-5 | 5 | 0 | 0
Y1 | 1 | 2520 25Mhz |  | 2520 24GND | 5 | 0 | 0

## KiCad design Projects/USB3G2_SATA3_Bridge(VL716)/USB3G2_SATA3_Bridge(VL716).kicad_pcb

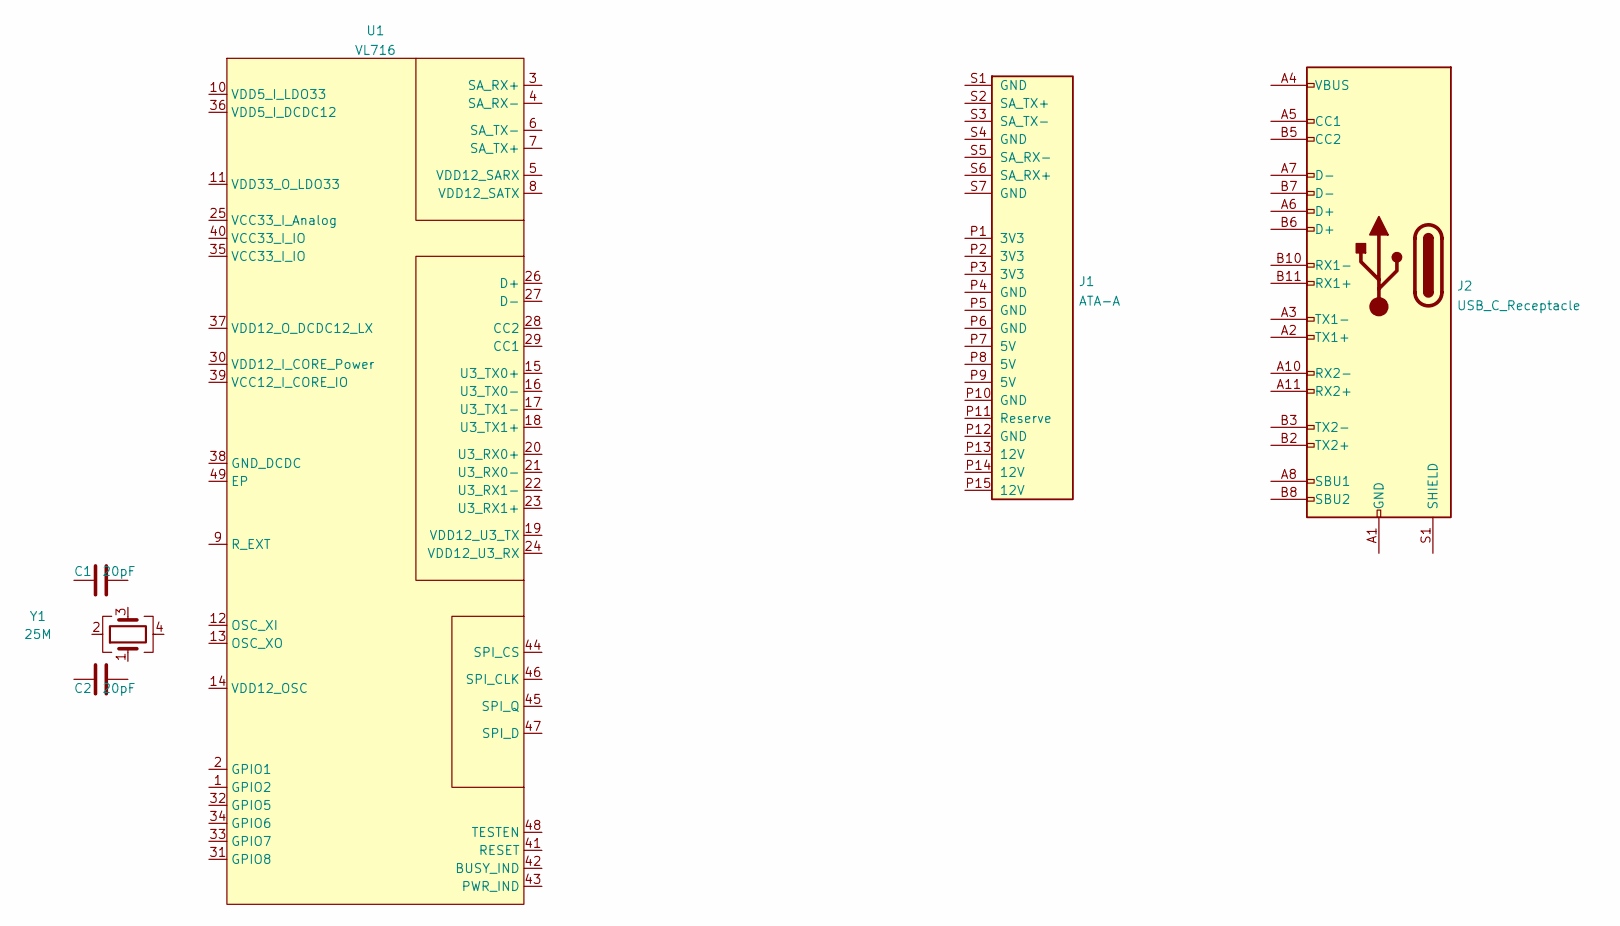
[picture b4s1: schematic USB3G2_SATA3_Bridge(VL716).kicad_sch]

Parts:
C1, C2: 20pF; C_0402_1005Metric
J1: ATA-A; SATA-22P-M
J2: USB_C_Receptacle; USB-C_24p
U1: VL716; QFN-48-1EP_6x6mm_P0.4mm_EP4.3x4.3mm
Y1: 25M; Crystal_SMD_2016-4Pin_2.0x1.6mm

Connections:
unnamed: J2.A1 (GND), J2.A12 (GND), J2.B1 (GND), J2.B12 (GND)
unnamed: J2.A4 (VBUS), J2.A9 (VBUS), J2.B4 (VBUS), J2.B9 (VBUS)

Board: 2 copper layers, 6 parts (0 on the bottom side), 2 nets, no tracks yet.
